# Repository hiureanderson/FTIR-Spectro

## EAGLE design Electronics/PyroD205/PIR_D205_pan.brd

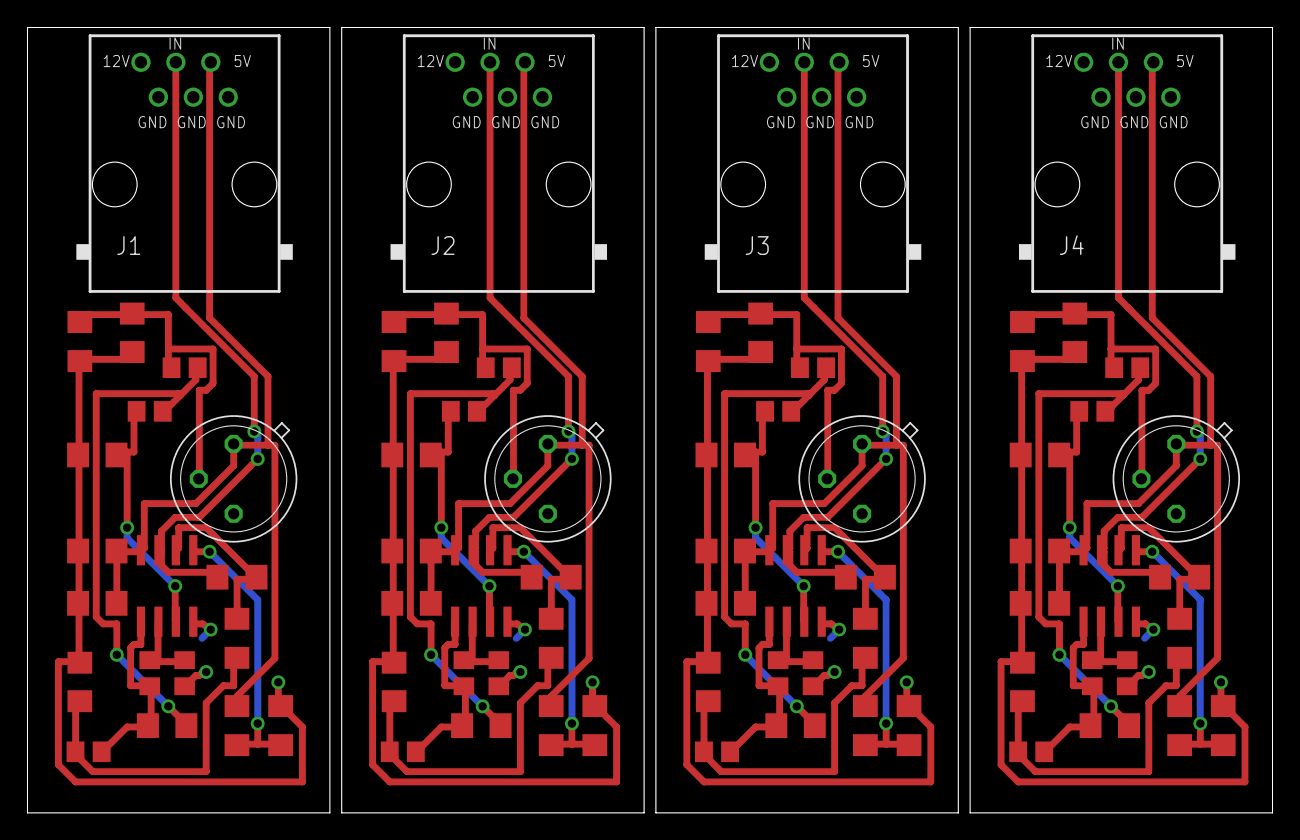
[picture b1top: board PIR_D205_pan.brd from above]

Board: 2 copper layers, 90.6 x 57.1 mm, 76 parts (0 on the bottom side), 44 nets.

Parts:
C1, C2, C3, C7, C8, C9, C13, C14, C15, C19, C20, C21: 4.7uF; C1206
C4, C6, C10, C12, C16, C18, C22, C24: 100nF; C1206
C5, C11, C17, C23: 10uF; C1206
IC1, IC2, IC3, IC4: TL072D; SO08
J1, J2, J3, J4: RJ12STRAIGHT-ANALOG; RJ12-STRAIGHT-ANALOG
R1, R11, R21, R31: 47k; R1206
R2, R3, R4, R12, R13, R14, R22, R23, R24, R32, R33, R34: 10k; R0805
R5, R6, R15, R16, R25, R26, R35, R36: 1k; R0805
R7, R17, R27, R37: 91; R1206
R8, R18, R28, R38: 390k; R1206
R9, R19, R29, R39: 200k; R1206
R10, R20, R30, R40: 51; R1206
U$1, U$2, U$3, U$4: D205B; TO5

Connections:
GND: C1.2, C2.2, C4.2, C5.2, C6.2, IC1.4, J1.GND1, J1.GND2, J1.GND3, R1.2, R6.1, R10.2, U$1.G
GND1: C7.2, C8.2, C10.2, C11.2, C12.2, IC2.4, J2.GND1, J2.GND2, J2.GND3, R11.2, R16.1, R20.2, U$2.G
GND2: C13.2, C14.2, C16.2, C17.2, C18.2, IC3.4, J3.GND1, J3.GND2, J3.GND3, R21.2, R26.1, R30.2, U$3.G
GND3: C19.2, C20.2, C22.2, C23.2, C24.2, IC4.4, J4.GND1, J4.GND2, J4.GND3, R31.2, R36.1, R40.2, U$4.G
unnamed: C6.1, R1.1, R4.1, U$1.S
unnamed: C3.2, IC1.1, R2.1, R5.2
unnamed: IC1.2, R5.1, R6.2
unnamed: C1.1, R2.2, R7.1
unnamed: C2.1, IC1.3, R3.2
unnamed: C3.1, R3.1, R4.2
unnamed: IC1.6, R7.2, R8.1
unnamed: IC1.7, J1.IN, R8.2
unnamed: IC1.5, R9.1, R10.1
unnamed: C12.1, R11.1, R14.1, U$2.S
unnamed: C9.2, IC2.1, R12.1, R15.2
unnamed: IC2.2, R15.1, R16.2
unnamed: C7.1, R12.2, R17.1
unnamed: C8.1, IC2.3, R13.2
unnamed: C9.1, R13.1, R14.2
unnamed: IC2.6, R17.2, R18.1
unnamed: IC2.7, J2.IN, R18.2
unnamed: IC2.5, R19.1, R20.1
unnamed: C18.1, R21.1, R24.1, U$3.S
unnamed: C15.2, IC3.1, R22.1, R25.2
unnamed: IC3.2, R25.1, R26.2
unnamed: C13.1, R22.2, R27.1
unnamed: C14.1, IC3.3, R23.2
unnamed: C15.1, R23.1, R24.2
unnamed: IC3.6, R27.2, R28.1
unnamed: IC3.7, J3.IN, R28.2
unnamed: IC3.5, R29.1, R30.1
unnamed: C24.1, R31.1, R34.1, U$4.S
unnamed: C21.2, IC4.1, R32.1, R35.2
unnamed: IC4.2, R35.1, R36.2
unnamed: C19.1, R32.2, R37.1
unnamed: C20.1, IC4.3, R33.2
unnamed: C21.1, R33.1, R34.2
unnamed: IC4.6, R37.2, R38.1
unnamed: IC4.7, J4.IN, R38.2
unnamed: IC4.5, R39.1, R40.1
VCC: C4.1, C5.1, IC1.8, J1.+5V, R9.2, U$1.D
VCC1: C10.1, C11.1, IC2.8, J2.+5V, R19.2, U$2.D
VCC2: C16.1, C17.1, IC3.8, J3.+5V, R29.2, U$3.D
VCC3: C22.1, C23.1, IC4.8, J4.+5V, R39.2, U$4.D
